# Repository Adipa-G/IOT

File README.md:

Please refer to the readme in each folder

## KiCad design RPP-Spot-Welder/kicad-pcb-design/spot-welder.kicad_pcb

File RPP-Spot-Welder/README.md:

# Raspberry PI Pico Spot Welder
This is a code used in a spot welder designed to weld 18650 batteries.

### Setting Up
Install Micropython to your Raspberry PI Pico board following [these instructions](https://www.raspberrypi.com/documentation/microcontrollers/micropython.html)

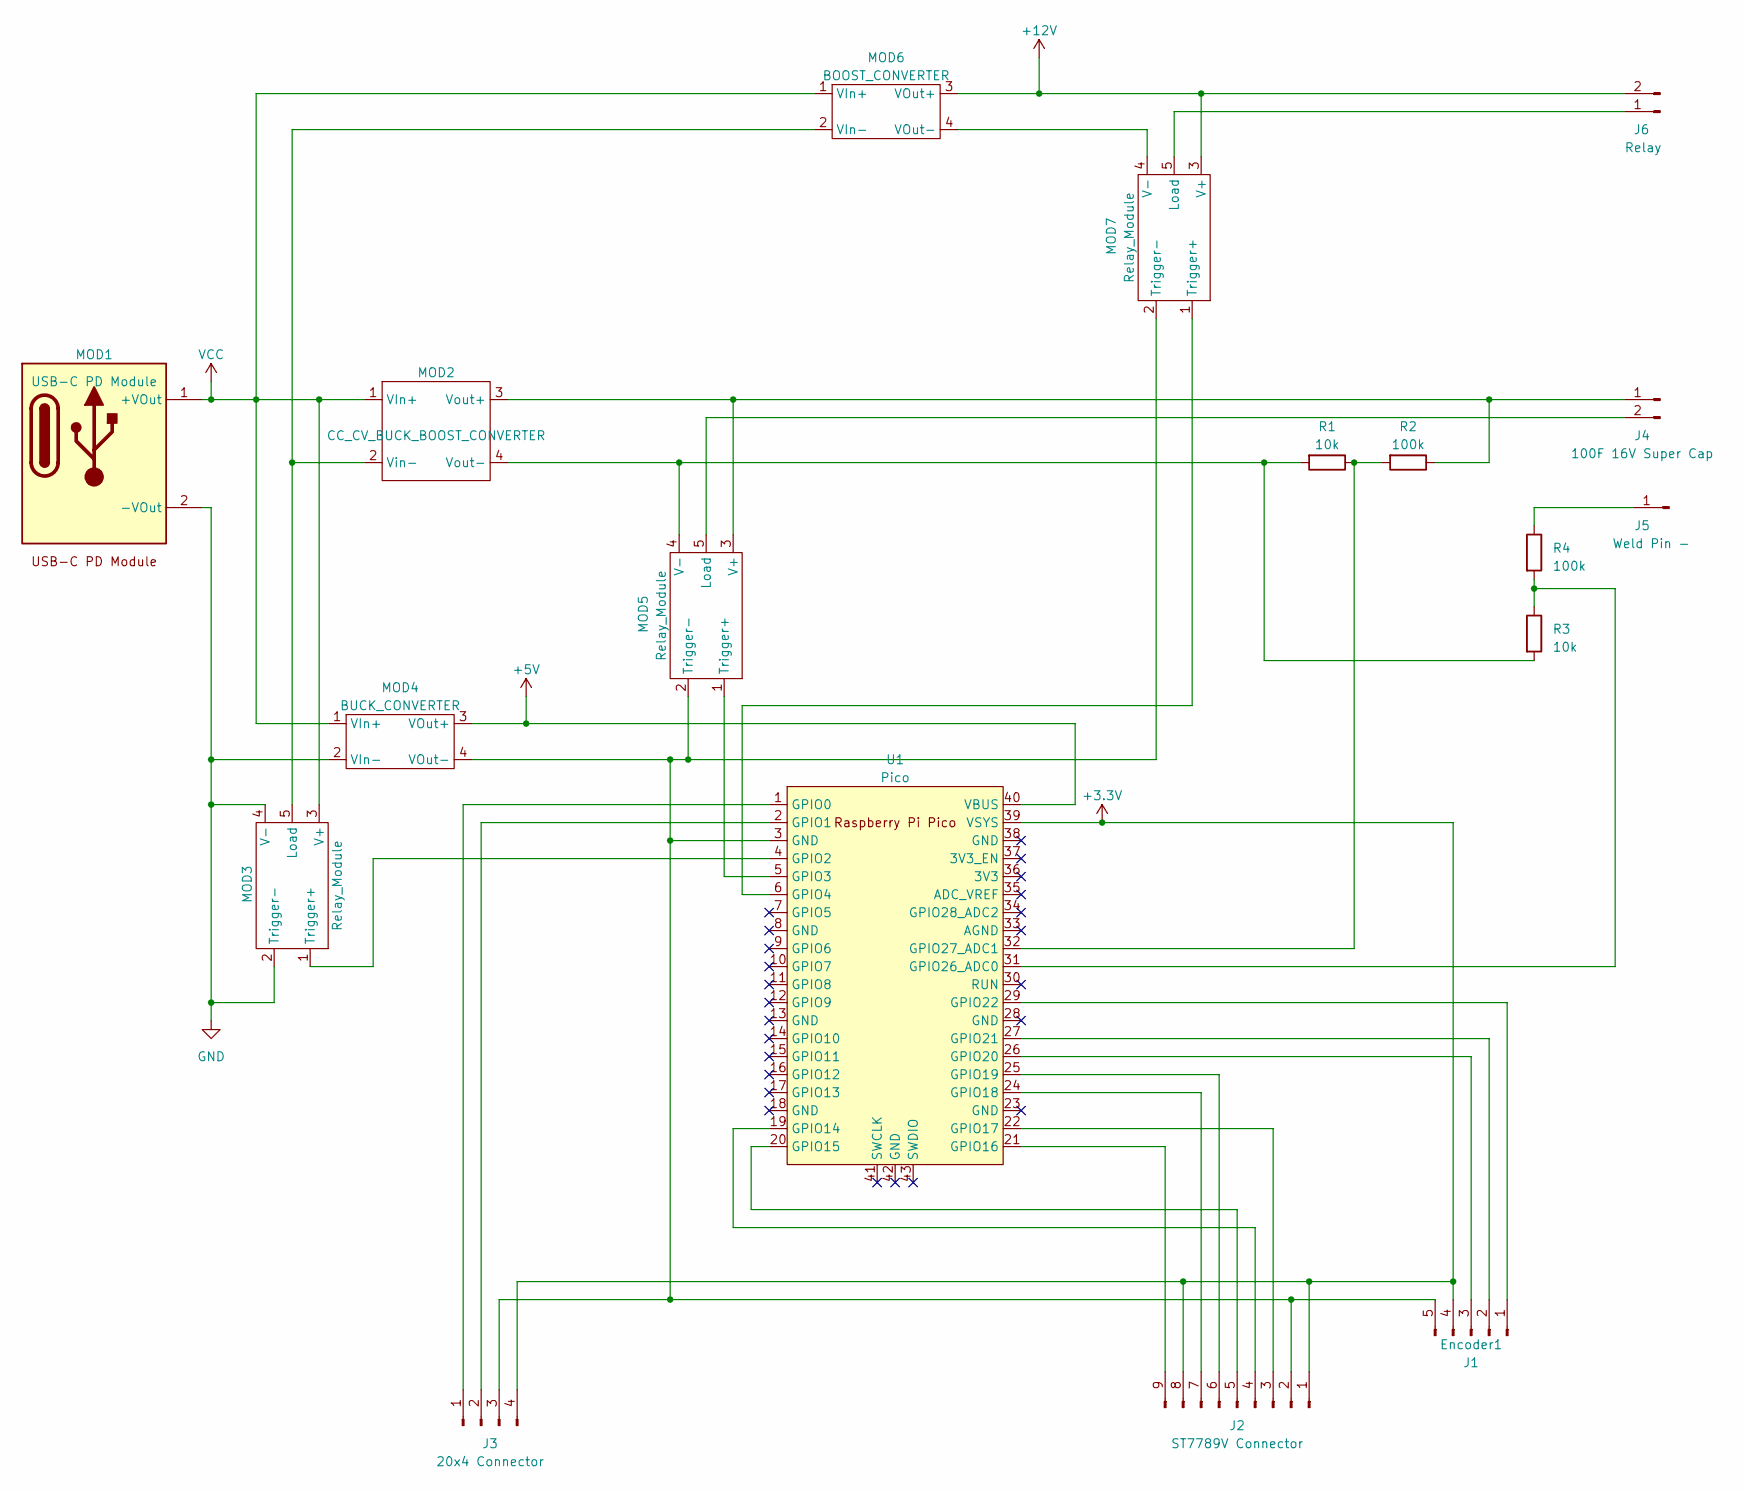
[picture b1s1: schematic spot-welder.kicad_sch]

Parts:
J1: Encoder1; JST_EH_B5B-EH-A_1x05_P2.50mm_Vertical
J2: ST7789V Connector; JST_EH_B9B-EH-A_1x09_P2.50mm_Vertical
J3: 20x4 Connector; JST_EH_B4B-EH-A_1x04_P2.50mm_Vertical
J4: 100F 16V Super Cap; JST_EH_B2B-EH-A_1x02_P2.50mm_Vertical
J5: Weld Pin -; JST_EH_B2B-EH-A_1x02_P2.50mm_Vertical
J6: Relay; JST_EH_B2B-EH-A_1x02_P2.50mm_Vertical
MOD1: USB-C PD Module; USBC_PD_Module
MOD2: CC_CV_BUCK_BOOST_CONVERTER
MOD3, MOD5, MOD7: Relay_Module
MOD4: BUCK_CONVERTER; BUCK_COVERTER
MOD6: BOOST_CONVERTER; BOOST_COVERTER
R1, R3: 10k; R_Axial_DIN0204_L3.6mm_D1.6mm_P1.90mm_Vertical
R2, R4: 100k; R_Axial_DIN0204_L3.6mm_D1.6mm_P1.90mm_Vertical
U1: Pico; RPi_Pico_SMD_TH

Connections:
+12V: J6.2, MOD6.3 (VOut+), MOD7.3 (V+)
GND: MOD1.2 (-VOut), MOD3.2 (Trigger-), MOD3.4 (V-), MOD4.2 (VIn-)
unnamed: J1.1, U1.29 (GPIO22)
unnamed: J1.2, U1.27 (GPIO21)
unnamed: J1.3, U1.26 (GPIO20)
unnamed: J1.5, J2.2, J3.3, MOD4.4 (VOut-), MOD5.2 (Trigger-), MOD7.2 (Trigger-), U1.3 (GND)
unnamed: J2.3, U1.22 (GPIO17)
unnamed: J2.4, U1.19 (GPIO14)
unnamed: J2.5, U1.20 (GPIO15)
unnamed: J2.6, U1.25 (GPIO19)
unnamed: J2.7, U1.24 (GPIO18)
unnamed: J2.9, U1.21 (GPIO16)
unnamed: J3.1, U1.1 (GPIO0)
unnamed: J3.2, U1.2 (GPIO1)
unnamed: J4.1, MOD2.3 (Vout+), MOD5.3 (V+), R2.1
unnamed: J4.2, MOD5.5 (Load)
unnamed: J5.1, R4.1
unnamed: J6.1, MOD7.5 (Load)
unnamed: MOD2.2 (Vin-), MOD3.5 (Load), MOD6.2 (VIn-)
unnamed: MOD2.4 (Vout-), MOD5.4 (V-), R1.2, R3.2
unnamed: MOD3.1 (Trigger+), U1.4 (GPIO2)
unnamed: MOD5.1 (Trigger+), U1.5 (GPIO3)
unnamed: MOD6.4 (VOut-), MOD7.4 (V-)
unnamed: MOD7.1 (Trigger+), U1.6 (GPIO4)
unnamed: R3.1, R4.2, U1.31 (GPIO26_ADC0)
unnamed: R1.1, R2.2, U1.32 (GPIO27_ADC1)
VCC: MOD1.1 (+VOut), MOD2.1 (VIn+), MOD3.3 (V+), MOD4.1 (VIn+), MOD6.1 (VIn+)

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
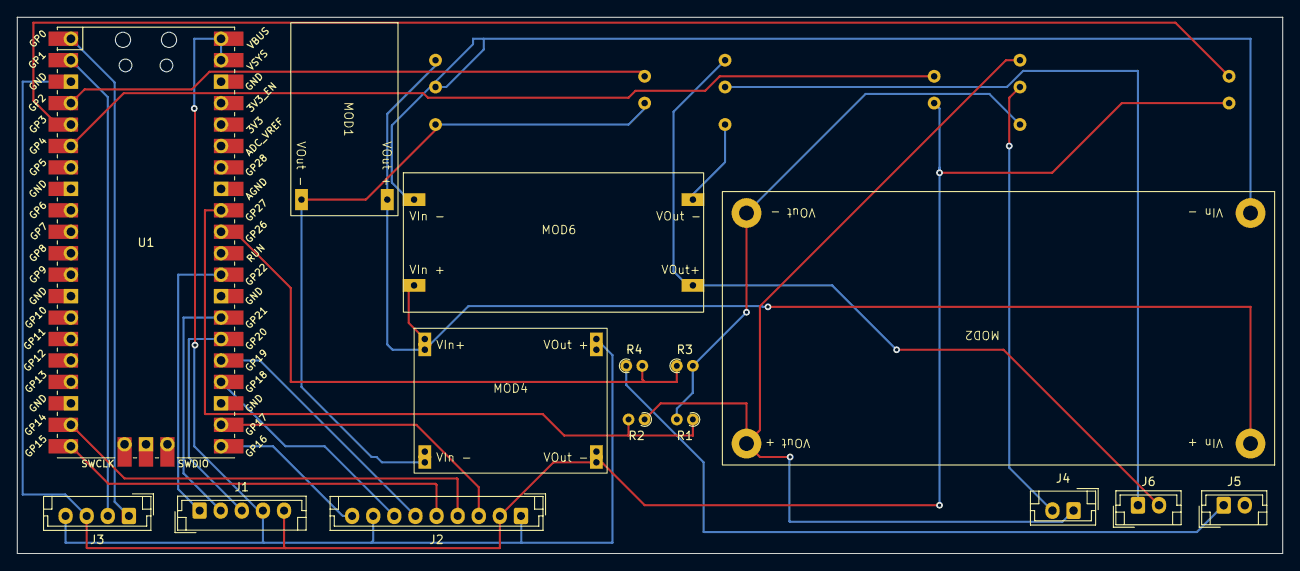
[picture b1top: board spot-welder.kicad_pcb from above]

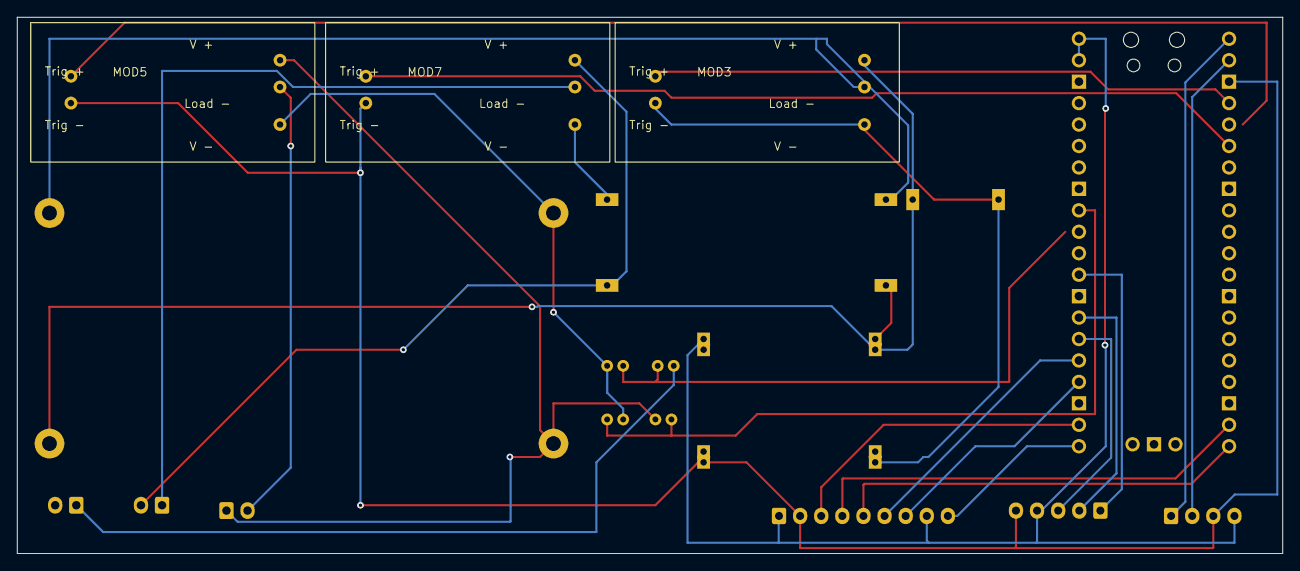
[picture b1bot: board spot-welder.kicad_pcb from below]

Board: 2 copper layers, 149.9 x 63.5 mm, 18 parts (3 on the bottom side), 28 nets.

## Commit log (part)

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2020-05-03 temp ESP 32 project
2020-05-10 ESP 32 project display stuff
2020-05-17 ESP 32 fixes
2021-04-13 fix image url
2021-04-13 ESP 32 water timer
2021-04-19 io schedule
2021-04-26 adding the pin controller
2021-05-03 timer status screen
2021-05-05 Dashboard screen
2021-05-17 power config screen
2021-05-18 cleanup
2021-05-18 fix spelling
2021-05-20 adding wifi config update
2021-05-23 adding reboot option
2021-06-02 adding captive portal
2021-06-05 doco
2021-09-05 wifi retry mechanism
2021-09-20 adding voltage sensor pin
2021-10-11 update doco
2022-01-12 fix times
2022-01-23 add basic kalman filter to filter voltage noise
2022-05-22 disable file write to prevent corrupt file system
2022-12-13 actions
2022-12-13 Bump decode-uri-component from 0.2.0 to 0.2.2 in /ESP32-Scheduler/web-ui
    Bumps [decode-uri-component](https://github.com/SamVerschueren/decode-uri-component) from 0.2.0 to 0.2.2.
    - [Release notes](https://github.com/SamVerschueren/decode-uri-component/releases)
    - [Commits](https://github.com/SamVerschueren/decode-uri-component/compare/v0.2.0...v0.2.2)
    ---
    updated-dependencies:
    - dependency-name: decode-uri-component
2022-12-13 Bump qs from 6.5.2 to 6.5.3 in /ESP32-Scheduler/web-ui
    Bumps [qs](https://github.com/ljharb/qs) from 6.5.2 to 6.5.3.
    - [Release notes](https://github.com/ljharb/qs/releases)
    - [Changelog](https://github.com/ljharb/qs/blob/main/CHANGELOG.md)
    - [Commits](https://github.com/ljharb/qs/compare/v6.5.2...v6.5.3)
    ---
    updated-dependencies:
2022-12-13 Bump loader-utils and react-scripts in /ESP32-Scheduler/web-ui
    Bumps [loader-utils](https://github.com/webpack/loader-utils) to 2.0.4 and updates ancestor dependency [react-scripts](https://github.com/facebook/create-react-app/tree/HEAD/packages/react-scripts). 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
    Updates `loader-utils` from 1.2.3 to 2.0.4
    - [Release notes](https://github.com/webpack/loader-utils/releases)
    - [Changelog](https://github.com/webpack/loader-utils/blob/v2.0.4/CHANGELOG.md)
    - [Commits](https://github.com/webpack/loader-utils/compare/v1.2.3...v2.0.4)
    Updates `react-scripts` from 4.0.0 to 5.0.1
2023-04-19 start the project spot welder
2023-04-19 Bump json5 from 1.0.1 to 1.0.2 in /ESP32-Scheduler/web-ui
    Bumps [json5](https://github.com/json5/json5) from 1.0.1 to 1.0.2.
    - [Release notes](https://github.com/json5/json5/releases)
    - [Changelog](https://github.com/json5/json5/blob/main/CHANGELOG.md)
    - [Commits](https://github.com/json5/json5/compare/v1.0.1...v1.0.2)
    ---
    updated-dependencies:
2023-04-19 Bump minimatch and react-scripts in /ESP32-Scheduler/web-ui
    Bumps [minimatch](https://github.com/isaacs/minimatch) to 3.1.2 and updates ancestor dependency [react-scripts](https://github.com/facebook/create-react-app/tree/HEAD/packages/react-scripts). These d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
    Updates `minimatch` from 3.0.4 to 3.1.2
    - [Release notes](https://github.com/isaacs/minimatch/releases)
    - [Changelog](https://github.com/isaacs/minimatch/blob/main/changelog.md)
    - [Commits](https://github.com/isaacs/minimatch/compare/v3.0.4...v3.1.2)
    Updates `react-scripts` from 4.0.0 to 5.0.1
2023-05-30 update the design
2023-07-09 Bump tough-cookie and jsdom in /ESP32-Scheduler/web-ui
    Bumps [tough-cookie](https://github.com/salesforce/tough-cookie) and [jsdom](https://github.com/jsdom/jsdom). These dependencies needed to be updated together.
    Updates `tough-cookie` from 2.5.0 to 4.1.3
    - [Release notes](https://github.com/salesforce/tough-cookie/releases)
    - [Changelog](https://github.com/salesforce/tough-cookie/blob/master/CHANGELOG.md)
    - [Commits](https://github.com/salesforce/tough-cookie/compare/v2.5.0...v4.1.3)
    Updates `jsdom` from 16.4.0 to 16.7.0
2023-07-11 Bump semver from 5.7.1 to 5.7.2 in /ESP32-Scheduler/web-ui
    Bumps [semver](https://github.com/npm/node-semver) from 5.7.1 to 5.7.2.
    - [Release notes](https://github.com/npm/node-semver/releases)
    - [Changelog](https://github.com/npm/node-semver/blob/v5.7.2/CHANGELOG.md)
    - [Commits](https://github.com/npm/node-semver/compare/v5.7.1...v5.7.2)
    ---
    updated-dependencies:
2023-09-02 generic display
2023-09-05 both displays function
2023-09-05 encoder
2023-11-15 adding unit test example
2025-08-15 updated the react version to 18
2025-08-15 fix script
2025-08-25 add e2e for the rest of it
2025-08-25 bump router
2025-08-25 getting annoying react-bootstrap
2025-10-20 Bump playwright and @playwright/test in /ESP32-Scheduler/web-ui
    Bumps [playwright](https://github.com/microsoft/playwright) to 1.56.1 and updates ancestor dependency [@playwright/test](https://github.com/microsoft/playwright). These dependencies need to be update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
    Updates `playwright` from 1.54.2 to 1.56.1
    - [Release notes](https://github.com/microsoft/playwright/releases)
    - [Commits](https://github.com/microsoft/playwright/compare/v1.54.2...v1.56.1)
    Updates `@playwright/test` from 1.54.2 to 1.56.1
    - [Release notes](https://github.com/microsoft/playwright/releases)
2025-11-17 Bump js-yaml in /ESP32-Scheduler/web-ui
    Bumps and [js-yaml](https://github.com/nodeca/js-yaml). These dependencies needed to be updated together.
    Updates `js-yaml` from 3.14.1 to 3.14.2
    - [Changelog](https://github.com/nodeca/js-yaml/blob/master/CHANGELOG.md)
    - [Commits](https://github.com/nodeca/js-yaml/compare/3.14.1...3.14.2)
    Updates `js-yaml` from 4.1.0 to 4.1.1
    - [Changelog](https://github.com/nodeca/js-yaml/blob/master/CHANGELOG.md)
2025-11-26 Bump node-forge from 1.3.1 to 1.3.2 in /ESP32-Scheduler/web-ui
    Bumps [node-forge](https://github.com/digitalbazaar/forge) from 1.3.1 to 1.3.2.
    - [Changelog](https://github.com/digitalbazaar/forge/blob/main/CHANGELOG.md)
    - [Commits](https://github.com/digitalbazaar/forge/compare/v1.3.1...v1.3.2)
    ---
    updated-dependencies:
    - dependency-name: node-forge
2026-01-02 Bump node-forge from 1.3.1 to 1.3.3 in /ESP32-Scheduler/web-ui
    Bumps [node-forge](https://github.com/digitalbazaar/forge) from 1.3.1 to 1.3.3.
    - [Changelog](https://github.com/digitalbazaar/forge/blob/main/CHANGELOG.md)
    - [Commits](https://github.com/digitalbazaar/forge/compare/v1.3.1...v1.3.3)
    ---
    updated-dependencies:
    - dependency-name: node-forge
2026-01-08 Bump react-router from 7.8.2 to 7.12.0 in /ESP32-Scheduler/web-ui
    Bumps [react-router](https://github.com/remix-run/react-router/tree/HEAD/packages/react-router) from 7.8.2 to 7.12.0.
    - [Release notes](https://github.com/remix-run/react-router/releases)
    - [Changelog](https://github.com/remix-run/react-router/blob/main/packages/react-router/CHANGELOG.md)
    - [Commits](https://github.com/remix-run/react-router/commits/react-router@7.12.0/packages/react-router)
    ---
    updated-dependencies:
2026-01-21 Bump lodash from 4.17.21 to 4.17.23 in /ESP32-Scheduler/web-ui
    Bumps [lodash](https://github.com/lodash/lodash) from 4.17.21 to 4.17.23.
    - [Release notes](https://github.com/lodash/lodash/releases)
    - [Commits](https://github.com/lodash/lodash/compare/4.17.21...4.17.23)
    ---
    updated-dependencies:
    - dependency-name: lodash
2026-02-07 Bump webpack from 5.101.3 to 5.105.0 in /ESP32-Scheduler/web-ui
    Bumps [webpack](https://github.com/webpack/webpack) from 5.101.3 to 5.105.0.
    - [Release notes](https://github.com/webpack/webpack/releases)
    - [Changelog](https://github.com/webpack/webpack/blob/main/CHANGELOG.md)
    - [Commits](https://github.com/webpack/webpack/compare/v5.101.3...v5.105.0)
    ---
    updated-dependencies:
2026-02-12 Bump jsonpath from 1.1.1 to 1.2.1 in /ESP32-Scheduler/web-ui
    Bumps [jsonpath](https://github.com/dchester/jsonpath) from 1.1.1 to 1.2.1.
    - [Commits](https://github.com/dchester/jsonpath/commits/1.2.1)
    ---
    updated-dependencies:
    - dependency-name: jsonpath
    dependency-version: 1.2.1
2026-02-21 Bump ajv from 6.12.6 to 6.14.0 in /ESP32-Scheduler/web-ui
    Bumps [ajv](https://github.com/ajv-validator/ajv) from 6.12.6 to 6.14.0.
    - [Release notes](https://github.com/ajv-validator/ajv/releases)
    - [Commits](https://github.com/ajv-validator/ajv/compare/v6.12.6...v6.14.0)
    ---
    updated-dependencies:
    - dependency-name: ajv
2026-02-25 Bump minimatch in /ESP32-Scheduler/web-ui
    Bumps and [minimatch](https://github.com/isaacs/minimatch). These dependencies needed to be updated together.
    Updates `minimatch` from 3.1.2 to 3.1.4
    - [Changelog](https://github.com/isaacs/minimatch/blob/main/changelog.md)
    - [Commits](https://github.com/isaacs/minimatch/compare/v3.1.2...v3.1.4)
    Updates `minimatch` from 9.0.5 to 9.0.7
    - [Changelog](https://github.com/isaacs/minimatch/blob/main/changelog.md)
2026-02-27 Bump rollup from 2.79.2 to 2.80.0 in /ESP32-Scheduler/web-ui
    Bumps [rollup](https://github.com/rollup/rollup) from 2.79.2 to 2.80.0.
    - [Release notes](https://github.com/rollup/rollup/releases)
    - [Changelog](https://github.com/rollup/rollup/blob/v2.80.0/CHANGELOG.md)
    - [Commits](https://github.com/rollup/rollup/compare/v2.79.2...v2.80.0)
    ---
    updated-dependencies:
2026-03-01 Bump minimatch in /ESP32-Scheduler/web-ui
    Bumps and [minimatch](https://github.com/isaacs/minimatch). These dependencies needed to be updated together.
    Updates `minimatch` from 3.1.2 to 3.1.5
    - [Changelog](https://github.com/isaacs/minimatch/blob/main/changelog.md)
    - [Commits](https://github.com/isaacs/minimatch/compare/v3.1.2...v3.1.5)
    Updates `minimatch` from 9.0.5 to 9.0.9
    - [Changelog](https://github.com/isaacs/minimatch/blob/main/changelog.md)
2026-03-21 Bump flatted from 3.3.3 to 3.4.2 in /ESP32-Scheduler/web-ui
    Bumps [flatted](https://github.com/WebReflection/flatted) from 3.3.3 to 3.4.2.
    - [Commits](https://github.com/WebReflection/flatted/compare/v3.3.3...v3.4.2)
    ---
    updated-dependencies:
    - dependency-name: flatted
    dependency-version: 3.4.2
2026-03-25 Bump yaml in /ESP32-Scheduler/web-ui
    Bumps and [yaml](https://github.com/eemeli/yaml). These dependencies needed to be updated together.
    Updates `yaml` from 1.10.2 to 1.10.3
    - [Release notes](https://github.com/eemeli/yaml/releases)
    - [Commits](https://github.com/eemeli/yaml/compare/v1.10.2...v1.10.3)
    Updates `yaml` from 2.8.1 to 2.8.3
    - [Release notes](https://github.com/eemeli/yaml/releases)
2026-03-25 Bump picomatch from 2.3.1 to 2.3.2 in /ESP32-Scheduler/web-ui
    Bumps [picomatch](https://github.com/micromatch/picomatch) from 2.3.1 to 2.3.2.
    - [Release notes](https://github.com/micromatch/picomatch/releases)
    - [Changelog](https://github.com/micromatch/picomatch/blob/master/CHANGELOG.md)
    - [Commits](https://github.com/micromatch/picomatch/compare/2.3.1...2.3.2)
    ---
    updated-dependencies:
2026-03-29 Bump brace-expansion in /ESP32-Scheduler/web-ui
    Bumps and [brace-expansion](https://github.com/juliangruber/brace-expansion). These dependencies needed to be updated together.
    Updates `brace-expansion` from 1.1.12 to 1.1.13
    - [Release notes](https://github.com/juliangruber/brace-expansion/releases)
    - [Commits](https://github.com/juliangruber/brace-expansion/compare/v1.1.12...v1.1.13)
    Updates `brace-expansion` from 2.0.2 to 2.0.3
    - [Release notes](https://github.com/juliangruber/brace-expansion/releases)
2026-04-02 Bump lodash from 4.17.21 to 4.18.1 in /ESP32-Scheduler/web-ui
    Bumps [lodash](https://github.com/lodash/lodash) from 4.17.21 to 4.18.1.
    - [Release notes](https://github.com/lodash/lodash/releases)
    - [Commits](https://github.com/lodash/lodash/compare/4.17.21...4.18.1)
    ---
    updated-dependencies:
    - dependency-name: lodash
2026-04-08 Upgraded packages
2026-05-26 refactor #1
2026-05-26 refactor #2
2026-05-26 refactor #3
2026-05-26 refactor #5
2026-05-26 tests
